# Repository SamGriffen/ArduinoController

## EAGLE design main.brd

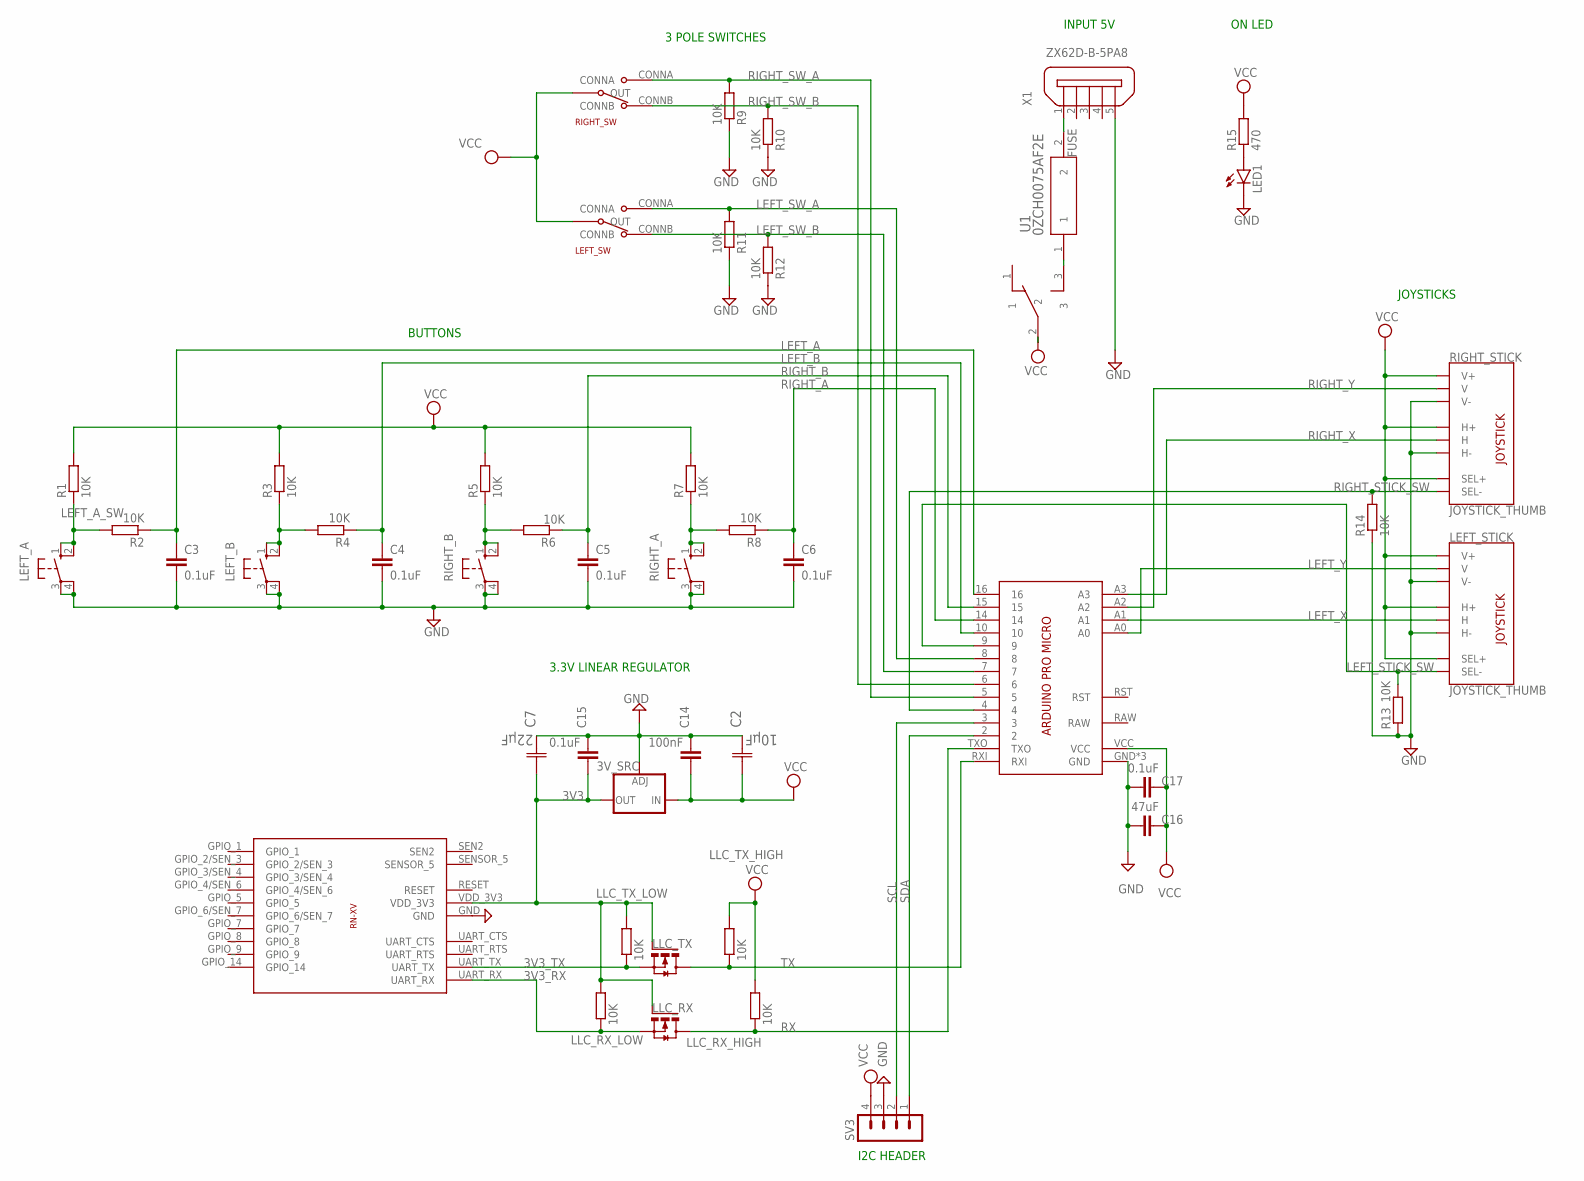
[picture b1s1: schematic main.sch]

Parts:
3V_SRC: V_REG_LM1117SOT223; SOT223
C2: 10µF; CAPCP6032X280N
C3, C4, C5, C6: 0.1uF; 0603
C7: 22µF; CAPCP3216X180N
C14: 100nF; C0805
C15, C17: 0.1uF; C0805
C16: 47uF; C0805
LED1: LED5MM
LEFT_A: 10-XX; B3F-10XX
LEFT_B: 10-XX; B3F-10XX
LEFT_STICK: JOYSTICK_THUMB; JOYSTICK
LEFT_SW: 2_POLE_SWITCH
LLC_RX: 2N7002,215; SOT23-3
LLC_RX_HIGH: 10K; R0805
LLC_RX_LOW: 10K; R0805
LLC_TX: 2N7002,215; SOT23-3
LLC_TX_HIGH: 10K; R0805
LLC_TX_LOW: 10K; R0805
R1, R2, R3, R4, R5, R6, R7, R8, R9, R10, R11, R12, R13, R14: 10K; R0805
R15: 470; R0805
RIGHT_A: 10-XX; B3F-10XX
RIGHT_B: 10-XX; B3F-10XX
RIGHT_STICK: JOYSTICK_THUMB; JOYSTICK
RIGHT_SW: 2_POLE_SWITCH
SV3: MA04-1
U1: 0ZCH0075AF2E; 0ZCH
U$1: ARDUINO_PRO_MICRO
U$2: RN-XV
U$4: EG1201
X1: ZX62D-B-5PA8

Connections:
3V3: 3V_SRC.2 (OUT), 3V_SRC.4 (OUT), C7.1 (C1), C15.1, LLC_RX.1 (G), LLC_RX_LOW.2, LLC_TX.1 (G), LLC_TX_LOW.2, U$2.VDD_3V3
3V3_RX: LLC_RX.2 (S), LLC_RX_LOW.1, U$2.UART_RX
3V3_TX: LLC_TX.2 (S), LLC_TX_LOW.1, U$2.UART_TX
FUSE: U1.2, X1.1
GND: 3V_SRC.1 (ADJ), C2.2 (C2), C3.2, C4.2, C5.2, C6.2, C7.2 (C2), C14.2, C15.2, C16.2, C17.2, LED1.K (C), LEFT_A.3, LEFT_A.4 (P1), LEFT_B.3, LEFT_B.4 (P1), LEFT_STICK.H3 (H-), LEFT_STICK.V3 (V-), R9.1, R10.1, R11.1, R12.1, R13.1, R14.1, RIGHT_A.3, RIGHT_A.4 (P1), RIGHT_B.3, RIGHT_B.4 (P1), RIGHT_STICK.H3 (H-), RIGHT_STICK.V3 (V-), SV3.3, U$1.GND, U$1.GND2 (GND), U$1.GND3 (GND), U$2.GND, X1.5
LEFT_A: C3.1, R2.1, U$1.16
LEFT_A_SW: LEFT_A.1 (S), LEFT_A.2 (S1), R1.1, R2.2
LEFT_B: C4.1, R4.1, U$1.10
LEFT_B_SW: LEFT_B.1 (S), LEFT_B.2 (S1), R3.1, R4.2
LEFT_STICK_SW: LEFT_STICK.B2A (SEL-), R13.2, U$1.9
LEFT_SW_A: LEFT_SW.CONNA, R11.2, U$1.8
LEFT_SW_B: LEFT_SW.CONNB, R12.2, U$1.7
LEFT_X: LEFT_STICK.H2 (H), U$1.A1
LEFT_Y: LEFT_STICK.V2 (V), U$1.A0
unnamed: LED1.A, R15.1
unnamed: U1.1, U$4.3
RIGHT_A: C6.1, R8.1, U$1.14
RIGHT_A_SW: R7.1, R8.2, RIGHT_A.1 (S), RIGHT_A.2 (S1)
RIGHT_B: C5.1, R6.1, U$1.15
RIGHT_B_SW: R5.1, R6.2, RIGHT_B.1 (S), RIGHT_B.2 (S1)
RIGHT_STICK_SW: R14.2, RIGHT_STICK.B2A (SEL-), U$1.4
RIGHT_SW_A: R9.2, RIGHT_SW.CONNA, U$1.5
RIGHT_SW_B: R10.2, RIGHT_SW.CONNB, U$1.6
RIGHT_X: RIGHT_STICK.H2 (H), U$1.A3
RIGHT_Y: RIGHT_STICK.V2 (V), U$1.A2
RX: LLC_RX.3 (D), LLC_RX_HIGH.1, U$1.TXO
SCL: SV3.2, U$1.3
SDA: SV3.1, U$1.2
TX: LLC_TX.3 (D), LLC_TX_HIGH.1, U$1.RXI
VCC: 3V_SRC.3 (IN), C2.1 (C1), C14.1, C16.1, C17.1, LEFT_STICK.B1A (SEL+), LEFT_STICK.H1 (H+), LEFT_STICK.V1 (V+), LEFT_SW.OUT, LLC_RX_HIGH.2, LLC_TX_HIGH.2, R1.2, R3.2, R5.2, R7.2, R15.2, RIGHT_STICK.B1A (SEL+), RIGHT_STICK.H1 (H+), RIGHT_STICK.V1 (V+), RIGHT_SW.OUT, SV3.4, U$1.VCC, U$4.2

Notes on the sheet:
3.3V LINEAR REGULATOR
BUTTONS
JOYSTICKS
3 POLE SWITCHES
INPUT 5V
ON LED
I2C HEADER

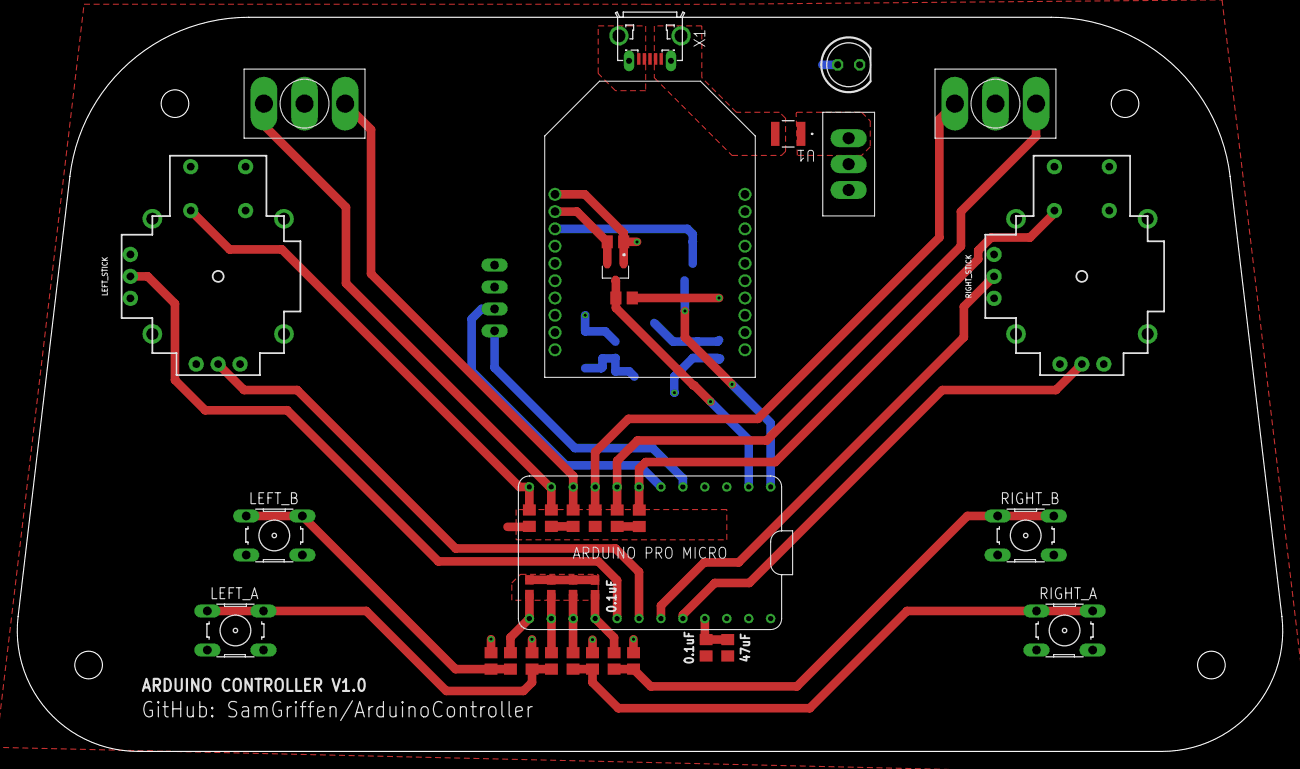
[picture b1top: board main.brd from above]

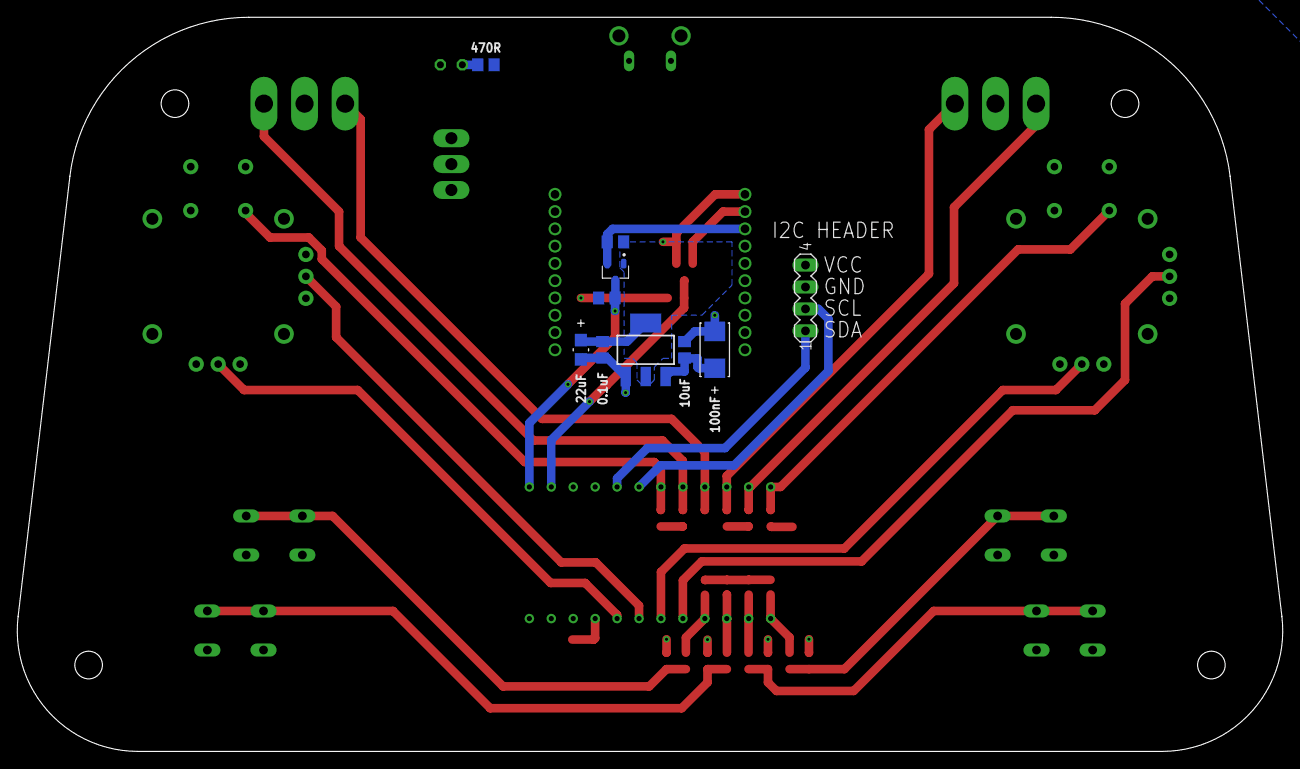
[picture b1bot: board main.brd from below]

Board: 2 copper layers, 146.5 x 85.0 mm, 47 parts (10 on the bottom side), 30 nets.

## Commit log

2019-08-22 FIle Changes
    Shifted images to an "images" directory
2019-08-22 Added Libraries
2019-08-23 Incorporated Feedback
2019-09-03 Small changes (?)
2019-09-04 Made AA mount
2019-09-05 Minor positioning changes
2019-09-05 Made silkscreen touches
2019-09-05 Added board version number
2019-09-06 Final version 1 changes

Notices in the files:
parts and their libraries:
SparkFun-Switches: Licensing: Creative Commons ShareAlike 4.0 International - https://creativecommons.org/licenses/by-sa/4.0
